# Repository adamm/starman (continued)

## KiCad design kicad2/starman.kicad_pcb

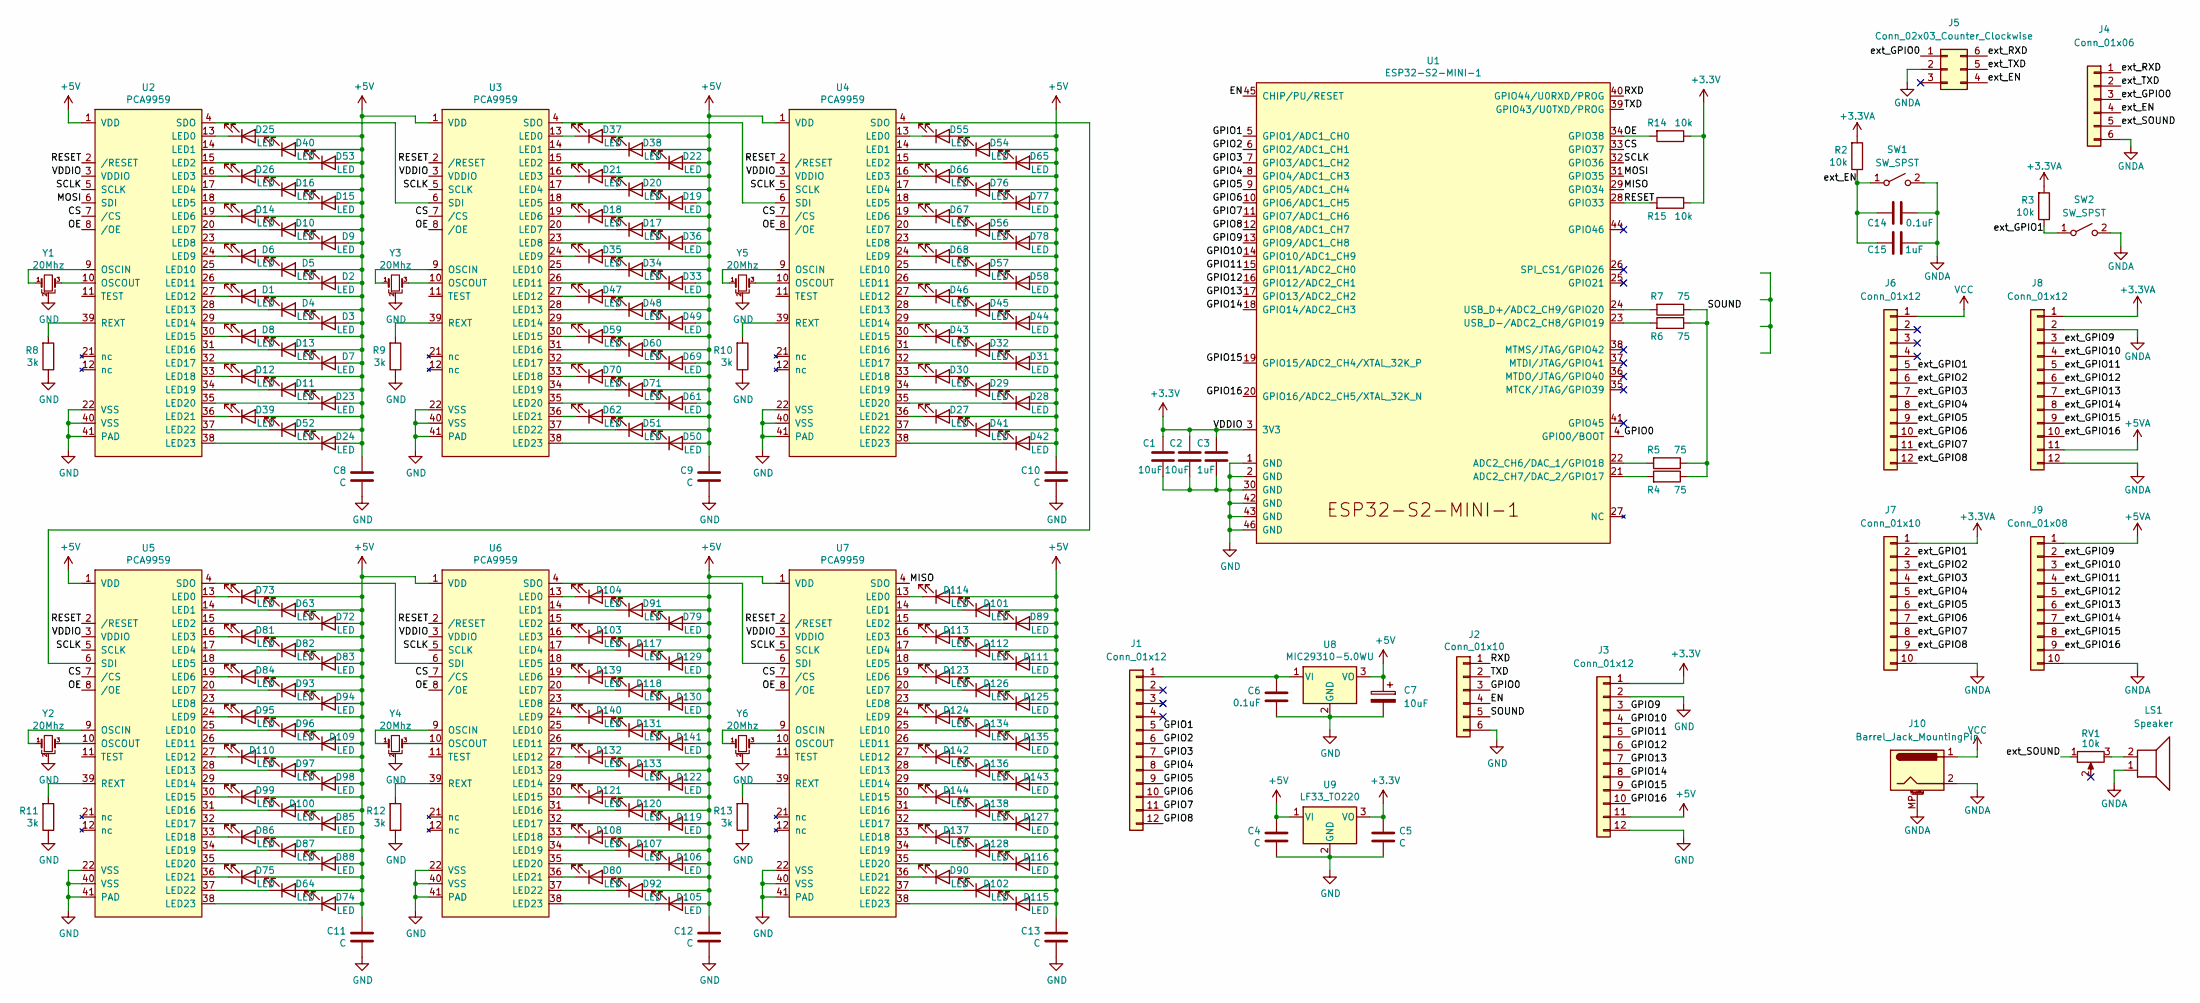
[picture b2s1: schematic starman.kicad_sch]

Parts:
C1, C2: 10uF; C_0805_2012Metric
C3, C15: 1uF; C_0805_2012Metric
C4, C5, C8, C9, C10, C11, C12, C13: C; C_0805_2012Metric
C6, C14: 0.1uF; C_0805_2012Metric
C7: 10uF; CP_EIA-3216-10_Kemet-I
D1, D2, D3, D4, D5, D6, D7, D8, D9, D10, D11, D12, D13, D14, D15, D16, D17, D18, D19, D20, D21, D22, D23, D24, D25, D26, D27, D28, D29, D30, D31, D32, D33, D34, D35, D36, D37, D38, D39, D40, D41, D42, D43, D44, D45, D46, D47, D48, D49, D50, D51, D52, D53, D54, D55, D56, D57, D58, D59, D60, D61, D62, D63, D64, D65, D66, D67, D68, D69, D70, D71, D72, D73, D74, D75, D76, D77, D78, D79, D80, D81, D82, D83, D84, D85, D86, D87, D88, D89, D90, D91, D92, D93, D94, D95, D96, D97, D98, D99, D100, D101, D102, D103, D104, D105, D106, D107, D108, D109, D110, D111, D112, D113, D114, D115, D116, D117, D118, D119, D120, D121, D122, D123, D124, D125, D126, D127, D128, D129, D130, D131, D132, D133, D134, D135, D136, D137, D138, D139, D140, D141, D142, D143, D144: LED; LED_Osram_Lx_P47F_D2mm_ReverseMount
J1: Conn_01x12; PinSocket_1x12_P2.54mm_Vertical_SMD_Pin1Right
J2: Conn_01x10; PinSocket_1x06_P2.54mm_Vertical_SMD_Pin1Left
J3: Conn_01x12; PinSocket_1x12_P2.54mm_Vertical_SMD_Pin1Left
J4: Conn_01x06; PinHeader_1x06_P2.54mm_Vertical
J5: Conn_02x03_Counter_Clockwise; PinHeader_2x03_P2.54mm_Vertical
J6, J8: Conn_01x12; PinHeader_1x12_P2.54mm_Vertical
J7: Conn_01x10; PinHeader_1x10_P2.54mm_Vertical
J9: Conn_01x08; PinHeader_1x10_P2.54mm_Vertical
J10: Barrel_Jack_MountingPin; BarrelJack_CUI_PJ-063AH_Horizontal
LS1: Speaker; MagneticBuzzer_StarMicronics_HMB-06_HMB-12
R2, R3, R14, R15: 10k; R_0805_2012Metric
R4, R5, R6, R7: 75; R_0805_2012Metric
R8, R9, R10, R11, R12, R13: 3k; R_0805_2012Metric
RV1: 10k; Potentiometer_ACP_CA9-VSMD_Vertical
SW1, SW2: SW_SPST; SW_SPST_PTS810
U1: ESP32-S2-MINI-1
U2, U3, U4, U5, U6, U7: PCA9959; QFN-40_EP_5x5_Pitch0.4mm
U8: MIC29310-5.0WU; TO-263-3_TabPin2
U9: LF33_TO220; SOT-223-3_TabPin2
Y1, Y2, Y3, Y4, Y5, Y6: 20Mhz; Resonator_SMD_muRata_CSTxExxV-3Pin_3.0x1.1mm

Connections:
+3.3VA: J7.1, J8.1, R2.2, R3.2
+3V3: C1.2, C2.2, C3.2, C5.2, J3.1, R14.1, R15.1, U1.3 (3V3), U2.3 (VDDIO), U3.3 (VDDIO), U4.3 (VDDIO), U5.3 (VDDIO), U6.3 (VDDIO), U7.3 (VDDIO), U9.3 (VO)
+5V: C4.2, C7.1, C8.2, C9.2, C10.2, C11.2, C12.2, C13.2, D1.2 (A), D2.2 (A), D3.2 (A), D4.2 (A), D5.2 (A), D6.2 (A), D7.2 (A), D8.2 (A), D9.2 (A), D10.2 (A), D11.2 (A), D12.2 (A), D13.2 (A), D14.2 (A), D15.2 (A), D16.2 (A), D17.2 (A), D18.2 (A), D19.2 (A), D20.2 (A), D21.2 (A), D22.2 (A), D23.2 (A), D24.2 (A), D25.2 (A), D26.2 (A), D27.2 (A), D28.2 (A), D29.2 (A), D30.2 (A), D31.2 (A), D32.2 (A), D33.2 (A), D34.2 (A), D35.2 (A), D36.2 (A), D37.2 (A), D38.2 (A), D39.2 (A), D40.2 (A), D41.2 (A), D42.2 (A), D43.2 (A), D44.2 (A), D45.2 (A), D46.2 (A), D47.2 (A), D48.2 (A), D49.2 (A), D50.2 (A), D51.2 (A), D52.2 (A), D53.2 (A), D54.2 (A), D55.2 (A), D56.2 (A), D57.2 (A), D58.2 (A), D59.2 (A), D60.2 (A), D61.2 (A), D62.2 (A), D63.2 (A), D64.2 (A), D65.2 (A), D66.2 (A), D67.2 (A), D68.2 (A), D69.2 (A), D70.2 (A), D71.2 (A), D72.2 (A), D73.2 (A), D74.2 (A), D75.2 (A), D76.2 (A), D77.2 (A), D78.2 (A), D79.2 (A), D80.2 (A), D81.2 (A), D82.2 (A), D83.2 (A), D84.2 (A), D85.2 (A), D86.2 (A), D87.2 (A), D88.2 (A), D89.2 (A), D90.2 (A), D91.2 (A), D92.2 (A), D93.2 (A), D94.2 (A), D95.2 (A), D96.2 (A), D97.2 (A), D98.2 (A), D99.2 (A), D100.2 (A), D101.2 (A), D102.2 (A), D103.2 (A), D104.2 (A), D105.2 (A), D106.2 (A), D107.2 (A), D108.2 (A), D109.2 (A), D110.2 (A), D111.2 (A), D112.2 (A), D113.2 (A), D114.2 (A), D115.2 (A), D116.2 (A), D117.2 (A), D118.2 (A), D119.2 (A), D120.2 (A), D121.2 (A), D122.2 (A), D123.2 (A), D124.2 (A), D125.2 (A), D126.2 (A), D127.2 (A), D128.2 (A), D129.2 (A), D130.2 (A), D131.2 (A), D132.2 (A), D133.2 (A), D134.2 (A), D135.2 (A), D136.2 (A), D137.2 (A), D138.2 (A), D139.2 (A), D140.2 (A), D141.2 (A), D142.2 (A), D143.2 (A), D144.2 (A), J3.11, U2.1 (VDD), U3.1 (VDD), U4.1 (VDD), U5.1 (VDD), U6.1 (VDD), U7.1 (VDD), U8.3 (VO), U9.1 (VI)
+5VA: J8.11, J9.1
/CS: U1.33 (GPIO37), U2.7 (/CS), U3.7 (/CS), U4.7 (/CS), U5.7 (/CS), U6.7 (/CS), U7.7 (/CS)
/EN: J2.4, U1.45 (CHIP/PU/RESET)
/GPIO0: J2.3, U1.4 (GPIO0/BOOT)
/GPIO1: J1.5, U1.5 (GPIO1/ADC1_CH0)
/GPIO2: J1.6, U1.6 (GPIO2/ADC1_CH1)
/GPIO3: J1.7, U1.7 (GPIO3/ADC1_CH2)
/GPIO4: J1.8, U1.8 (GPIO4/ADC1_CH3)
/GPIO5: J1.9, U1.9 (GPIO5/ADC1_CH4)
/GPIO6: J1.10, U1.10 (GPIO6/ADC1_CH5)
/GPIO7: J1.11, U1.11 (GPIO7/ADC1_CH6)
/GPIO8: J1.12, U1.12 (GPIO8/ADC1_CH7)
/GPIO9: J3.3, U1.13 (GPIO9/ADC1_CH8)
/GPIO10: J3.4, U1.14 (GPIO10/ADC1_CH9)
/GPIO11: J3.5, U1.15 (GPIO11/ADC2_CH0)
/GPIO12: J3.6, U1.16 (GPIO12/ADC2_CH1)
/GPIO13: J3.7, U1.17 (GPIO13/ADC2_CH2)
/GPIO14: J3.8, U1.18 (GPIO14/ADC2_CH3)
/GPIO15: J3.9, U1.19 (GPIO15/ADC2_CH4/XTAL_32K_P)
/GPIO16: J3.10, U1.20 (GPIO16/ADC2_CH5/XTAL_32K_N)
/MISO: U1.29 (GPIO34), U7.4 (SDO)
/MOSI: U1.31 (GPIO35), U2.6 (SDI)
/OE: R14.2, U1.34 (GPIO38), U2.8 (/OE), U3.8 (/OE), U4.8 (/OE), U5.8 (/OE), U6.8 (/OE), U7.8 (/OE)
/RESET: R15.2, U1.28 (GPIO33), U2.2 (/RESET), U3.2 (/RESET), U4.2 (/RESET), U5.2 (/RESET), U6.2 (/RESET), U7.2 (/RESET)
/RXD: J2.1, U1.40 (GPIO44/U0RXD/PROG)
/SCLK: U1.32 (GPIO36), U2.5 (SCLK), U3.5 (SCLK), U4.5 (SCLK), U5.5 (SCLK), U6.5 (SCLK), U7.5 (SCLK)
/SOUND: J2.5, R4.1, R5.1, R6.1, R7.1
/TXD: J2.2, U1.39 (GPIO43/U0TXD/PROG)
/ext_EN: C14.2, C15.2, J4.4, J5.4, R2.1, SW1.1 (A)
/ext_GPIO0: J4.3, J5.1
/ext_GPIO1: J6.5, J7.2, R3.1, SW2.1 (A)
/ext_GPIO2: J6.6, J7.3
/ext_GPIO3: J6.7, J7.4
/ext_GPIO4: J6.8, J7.5
/ext_GPIO5: J6.9, J7.6
/ext_GPIO6: J6.10, J7.7
/ext_GPIO7: J6.11, J7.8
/ext_GPIO8: J6.12, J7.9
/ext_GPIO9: J8.3, J9.2
/ext_GPIO10: J8.4, J9.3
/ext_GPIO11: J8.5, J9.4
/ext_GPIO12: J8.6, J9.5
/ext_GPIO13: J8.7, J9.6
/ext_GPIO14: J8.8, J9.7
/ext_GPIO15: J8.9, J9.8
/ext_GPIO16: J8.10, J9.9
/ext_RXD: J4.1, J5.6
/ext_SOUND: J4.5, RV1.1
/ext_TXD: J4.2, J5.5
GND: C1.1, C2.1, C3.1, C4.1, C5.1, C6.1, C7.2, C8.1, C9.1, C10.1, C11.1, C12.1, C13.1, J2.6, J3.2, J3.12, R8.1, R9.1, R10.1, R11.1, R12.1, R13.1, U1.1 (GND), U1.2 (GND), U1.30 (GND), U1.42 (GND), U1.43 (GND), U1.46 (GND), U2.22 (VSS), U2.40 (VSS), U2.41 (PAD), U3.22 (VSS), U3.40 (VSS), U3.41 (PAD), U4.22 (VSS), U4.40 (VSS), U4.41 (PAD), U5.22 (VSS), U5.40 (VSS), U5.41 (PAD), U6.22 (VSS), U6.40 (VSS), U6.41 (PAD), U7.22 (VSS), U7.40 (VSS), U7.41 (PAD), U8.2 (GND), U9.2 (GND), Y1.2, Y2.2, Y3.2, Y4.2, Y5.2, Y6.2
GNDA: C14.1, C15.1, J4.6, J5.2, J7.10, J8.2, J8.12, J9.10, J10.2, J10.MP (MountPin), LS1.1, SW1.2 (B), SW2.2 (B)
unnamed: C6.2, J1.1, U8.1 (VI)
unnamed: D1.1 (K), U2.27 (LED12)
unnamed: D2.1 (K), U2.26 (LED11)
unnamed: D3.1 (K), U2.29 (LED14)
unnamed: D4.1 (K), U2.28 (LED13)
unnamed: D5.1 (K), U2.25 (LED10)
unnamed: D6.1 (K), U2.24 (LED9)
unnamed: D7.1 (K), U2.32 (LED17)
unnamed: D8.1 (K), U2.30 (LED15)
unnamed: D9.1 (K), U2.23 (LED8)
unnamed: D10.1 (K), U2.20 (LED7)
unnamed: D11.1 (K), U2.34 (LED19)
unnamed: D12.1 (K), U2.33 (LED18)
unnamed: D13.1 (K), U2.31 (LED16)
unnamed: D14.1 (K), U2.19 (LED6)
unnamed: D15.1 (K), U2.18 (LED5)
unnamed: D16.1 (K), U2.17 (LED4)
unnamed: D17.1 (K), U3.20 (LED7)
unnamed: D18.1 (K), U3.19 (LED6)
unnamed: D19.1 (K), U3.18 (LED5)
unnamed: D20.1 (K), U3.17 (LED4)
unnamed: D21.1 (K), U3.16 (LED3)
unnamed: D22.1 (K), U3.15 (LED2)
unnamed: D23.1 (K), U2.35 (LED20)
unnamed: D24.1 (K), U2.38 (LED23)
unnamed: D25.1 (K), U2.13 (LED0)
unnamed: D26.1 (K), U2.16 (LED3)
unnamed: D27.1 (K), U4.36 (LED21)
unnamed: D28.1 (K), U4.35 (LED20)
unnamed: D29.1 (K), U4.34 (LED19)
unnamed: D30.1 (K), U4.33 (LED18)
unnamed: D31.1 (K), U4.32 (LED17)
unnamed: D32.1 (K), U4.31 (LED16)
unnamed: D33.1 (K), U3.26 (LED11)
unnamed: D34.1 (K), U3.25 (LED10)
unnamed: D35.1 (K), U3.24 (LED9)
unnamed: D36.1 (K), U3.23 (LED8)
unnamed: D37.1 (K), U3.13 (LED0)
unnamed: D38.1 (K), U3.14 (LED1)
unnamed: D39.1 (K), U2.36 (LED21)
unnamed: D40.1 (K), U2.14 (LED1)
unnamed: D41.1 (K), U4.37 (LED22)
unnamed: D42.1 (K), U4.38 (LED23)
unnamed: D43.1 (K), U4.30 (LED15)
unnamed: D44.1 (K), U4.29 (LED14)
unnamed: D45.1 (K), U4.28 (LED13)
unnamed: D46.1 (K), U4.27 (LED12)
unnamed: D47.1 (K), U3.27 (LED12)
unnamed: D48.1 (K), U3.28 (LED13)
unnamed: D49.1 (K), U3.29 (LED14)
unnamed: D50.1 (K), U3.38 (LED23)
unnamed: D51.1 (K), U3.37 (LED22)
unnamed: D52.1 (K), U2.37 (LED22)
unnamed: D53.1 (K), U2.15 (LED2)
unnamed: D54.1 (K), U4.14 (LED1)
unnamed: D55.1 (K), U4.13 (LED0)
unnamed: D56.1 (K), U4.20 (LED7)
unnamed: D57.1 (K), U4.25 (LED10)
unnamed: D58.1 (K), U4.26 (LED11)
unnamed: D59.1 (K), U3.30 (LED15)
unnamed: D60.1 (K), U3.31 (LED16)
unnamed: D61.1 (K), U3.35 (LED20)
unnamed: D62.1 (K), U3.36 (LED21)
unnamed: D63.1 (K), U5.14 (LED1)
unnamed: D64.1 (K), U5.37 (LED22)
unnamed: D65.1 (K), U4.15 (LED2)
unnamed: D66.1 (K), U4.16 (LED3)
unnamed: D67.1 (K), U4.19 (LED6)
unnamed: D68.1 (K), U4.24 (LED9)
unnamed: D69.1 (K), U3.32 (LED17)
unnamed: D70.1 (K), U3.33 (LED18)
unnamed: D71.1 (K), U3.34 (LED19)
unnamed: D72.1 (K), U5.15 (LED2)
unnamed: D73.1 (K), U5.13 (LED0)
unnamed: D74.1 (K), U5.38 (LED23)
unnamed: D75.1 (K), U5.36 (LED21)
unnamed: D76.1 (K), U4.17 (LED4)
unnamed: D77.1 (K), U4.18 (LED5)
unnamed: D78.1 (K), U4.23 (LED8)
unnamed: D79.1 (K), U6.15 (LED2)
unnamed: D80.1 (K), U6.36 (LED21)
unnamed: D81.1 (K), U5.16 (LED3)
unnamed: D82.1 (K), U5.17 (LED4)
unnamed: D83.1 (K), U5.18 (LED5)
unnamed: D84.1 (K), U5.19 (LED6)
unnamed: D85.1 (K), U5.32 (LED17)
unnamed: D86.1 (K), U5.33 (LED18)
unnamed: D87.1 (K), U5.34 (LED19)
unnamed: D88.1 (K), U5.35 (LED20)
unnamed: D89.1 (K), U7.15 (LED2)
unnamed: D90.1 (K), U7.36 (LED21)
unnamed: D91.1 (K), U6.14 (LED1)
unnamed: D92.1 (K), U6.37 (LED22)
unnamed: D93.1 (K), U5.20 (LED7)
unnamed: D94.1 (K), U5.23 (LED8)
unnamed: D95.1 (K), U5.24 (LED9)
unnamed: D96.1 (K), U5.25 (LED10)
unnamed: D97.1 (K), U5.28 (LED13)
unnamed: D98.1 (K), U5.29 (LED14)
unnamed: D99.1 (K), U5.30 (LED15)
unnamed: D100.1 (K), U5.31 (LED16)
unnamed: D101.1 (K), U7.14 (LED1)
unnamed: D102.1 (K), U7.37 (LED22)
unnamed: D103.1 (K), U6.16 (LED3)
unnamed: D104.1 (K), U6.13 (LED0)
unnamed: D105.1 (K), U6.38 (LED23)
unnamed: D106.1 (K), U6.35 (LED20)
unnamed: D107.1 (K), U6.34 (LED19)
unnamed: D108.1 (K), U6.33 (LED18)
unnamed: D109.1 (K), U5.26 (LED11)
unnamed: D110.1 (K), U5.27 (LED12)
unnamed: D111.1 (K), U7.18 (LED5)
unnamed: D112.1 (K), U7.17 (LED4)
unnamed: D113.1 (K), U7.16 (LED3)
unnamed: D114.1 (K), U7.13 (LED0)
unnamed: D115.1 (K), U7.38 (LED23)
unnamed: D116.1 (K), U7.35 (LED20)
unnamed: D117.1 (K), U6.17 (LED4)
unnamed: D118.1 (K), U6.20 (LED7)
unnamed: D119.1 (K), U6.32 (LED17)
unnamed: D120.1 (K), U6.31 (LED16)
unnamed: D121.1 (K), U6.30 (LED15)
unnamed: D122.1 (K), U6.29 (LED14)
unnamed: D123.1 (K), U7.19 (LED6)
unnamed: D124.1 (K), U7.24 (LED9)
unnamed: D125.1 (K), U7.23 (LED8)
unnamed: D126.1 (K), U7.20 (LED7)
unnamed: D127.1 (K), U7.32 (LED17)
unnamed: D128.1 (K), U7.34 (LED19)
unnamed: D129.1 (K), U6.18 (LED5)
unnamed: D130.1 (K), U6.23 (LED8)
unnamed: D131.1 (K), U6.25 (LED10)
unnamed: D132.1 (K), U6.27 (LED12)
unnamed: D133.1 (K), U6.28 (LED13)
unnamed: D134.1 (K), U7.25 (LED10)
unnamed: D135.1 (K), U7.26 (LED11)
unnamed: D136.1 (K), U7.28 (LED13)
unnamed: D137.1 (K), U7.33 (LED18)
unnamed: D138.1 (K), U7.31 (LED16)
unnamed: D139.1 (K), U6.19 (LED6)
unnamed: D140.1 (K), U6.24 (LED9)
unnamed: D141.1 (K), U6.26 (LED11)
unnamed: D142.1 (K), U7.27 (LED12)
unnamed: D143.1 (K), U7.29 (LED14)
unnamed: D144.1 (K), U7.30 (LED15)
unnamed: R4.2, U1.21 (ADC2_CH7/DAC_2/GPIO17)
unnamed: R5.2, U1.22 (ADC2_CH6/DAC_1/GPIO18)
unnamed: R6.2, U1.23 (USB_D-/ADC2_CH8/GPIO19)
unnamed: R7.2, U1.24 (USB_D+/ADC2_CH9/GPIO20)
unnamed: R8.2, U2.39 (REXT)
unnamed: R9.2, U3.39 (REXT)
unnamed: R10.2, U4.39 (REXT)
unnamed: R11.2, U5.39 (REXT)
unnamed: R12.2, U6.39 (REXT)
unnamed: R13.2, U7.39 (REXT)
unnamed: LS1.2, RV1.3
unnamed: U2.4 (SDO), U3.6 (SDI)
unnamed: U2.9 (OSCIN), Y1.1
unnamed: U2.10 (OSCOUT), Y1.3
unnamed: U3.4 (SDO), U4.6 (SDI)
unnamed: U3.9 (OSCIN), Y3.1
unnamed: U3.10 (OSCOUT), Y3.3
unnamed: U4.4 (SDO), U5.6 (SDI)
unnamed: U4.9 (OSCIN), Y5.1
unnamed: U4.10 (OSCOUT), Y5.3
unnamed: U5.4 (SDO), U6.6 (SDI)
unnamed: U5.9 (OSCIN), Y2.1
unnamed: U5.10 (OSCOUT), Y2.3
unnamed: U6.4 (SDO), U7.6 (SDI)
unnamed: U6.9 (OSCIN), Y4.1
unnamed: U6.10 (OSCOUT), Y4.3
unnamed: U7.9 (OSCIN), Y6.1
unnamed: U7.10 (OSCOUT), Y6.3
VCC: J6.1, J10.1

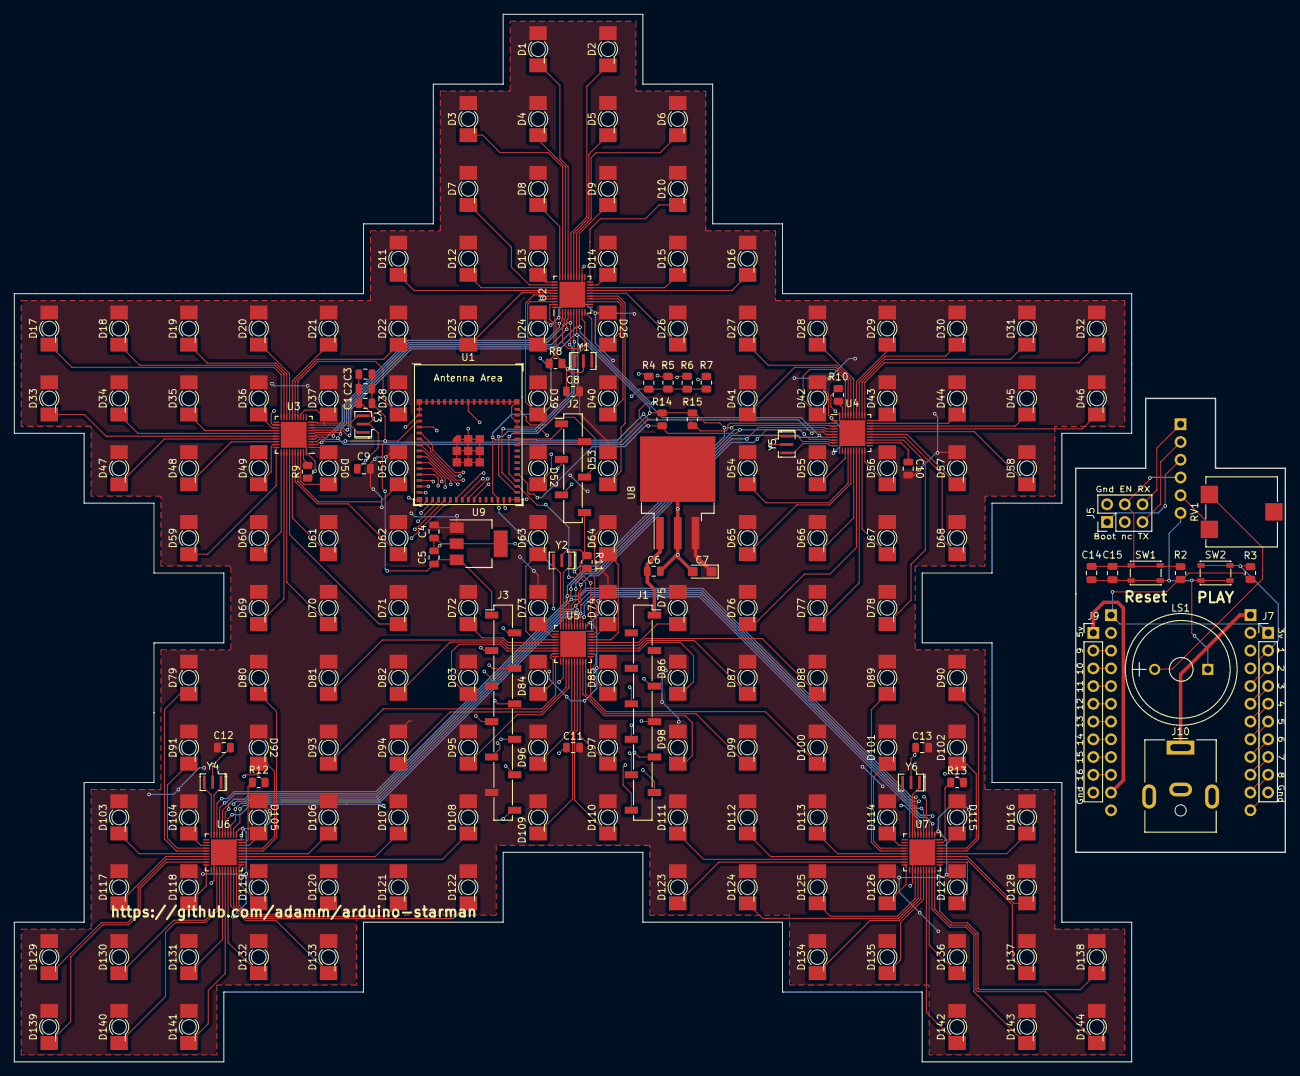
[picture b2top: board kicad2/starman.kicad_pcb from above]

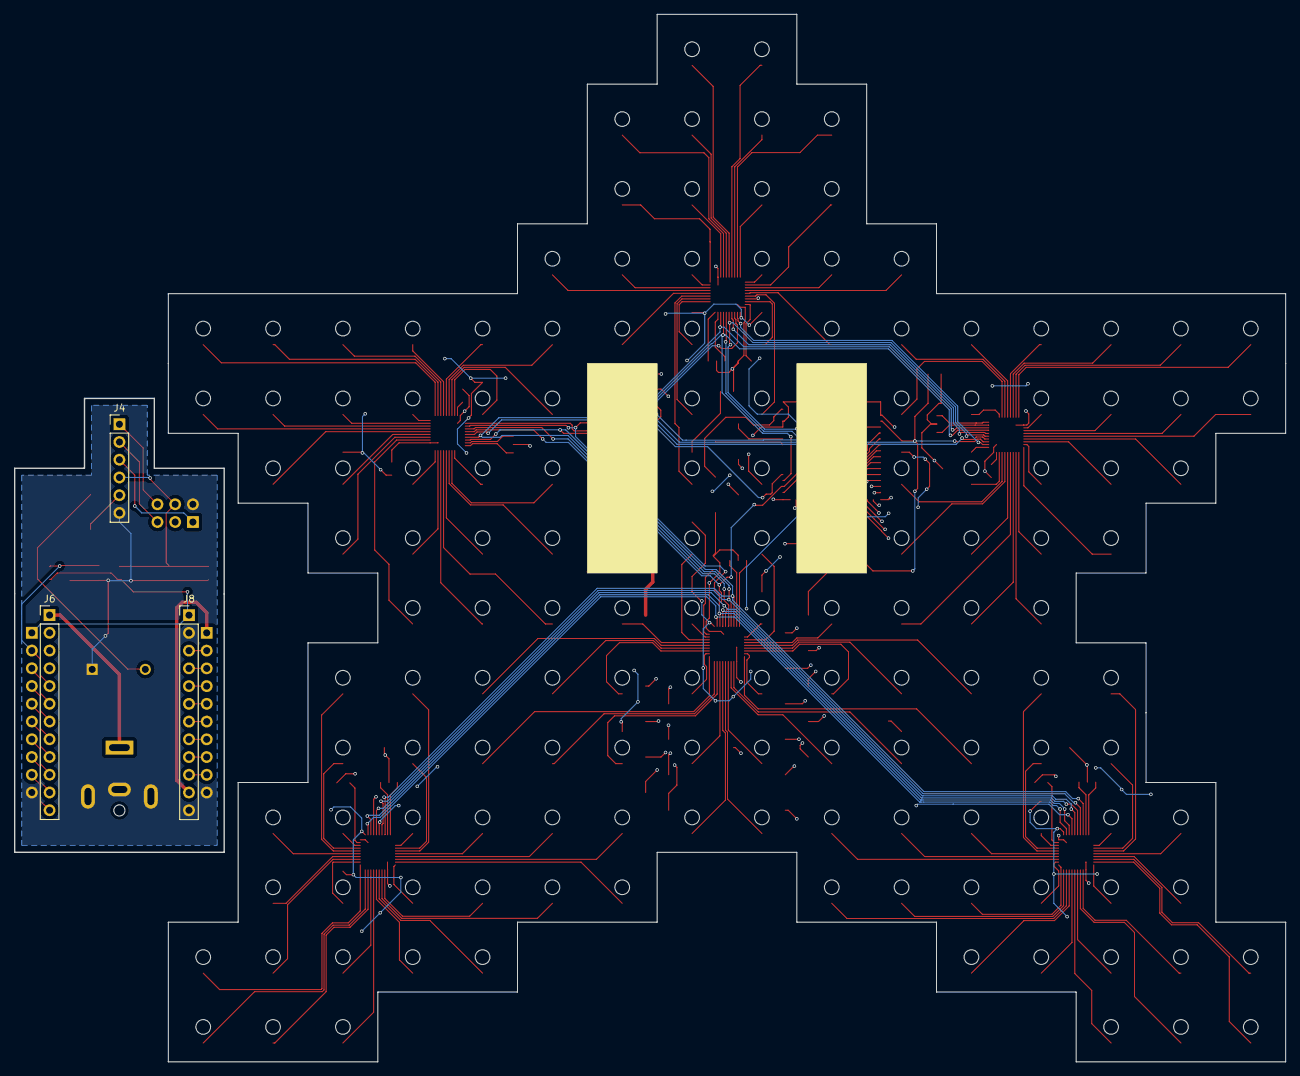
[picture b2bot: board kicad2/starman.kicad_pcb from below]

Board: 4 copper layers, 160.0 x 150.0 mm, 202 parts (3 on the bottom side), 228 nets.

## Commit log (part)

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2018-12-09 Updated the INO header
2018-12-09 Initial version of sparkly then crazy starman light array
2018-12-09 Include GNUv3 license to main code
    Adafruit TLC5947 code uses BSD license
2018-12-09 More README
2018-12-09 Include Playtune library
2018-12-15 Added Mario music tracks
    Converted from mariopiano.com MIDIs into C using converter at
    https://github.com/lenshustek/miditones
2018-12-15 Removed unused code, minor formatting adjustments
2018-12-16 Force a hardware reset after playback.
    For some reason, attachInterrupt() conflicts with pt.initchan()
    functions to the point after 2 or 3 music loops, the arduino hard-locks.
    As a workaround, execute a hardware reset after each loop. Not ideal
    but good enough: we don't need to track the state between runs.
2018-12-16 Add in additional music, and different sequencing/patterns based on the music being played
2021-11-28 Convert the playtune library to ESP32
    Based upon Teensy version created by original author
2021-11-28 Fixed crash under some marquee patterns (buffer overflow); also removed button interrupt (was overkill, caused crashes)
2021-11-29 Updated Overworld to SMBW version
2021-12-01 Strange bug where underwater crashes esp32 when debug logs are printed
    Need to figure out what\'s going on, but until then, just disable the logs!
2021-12-01 Add on a very basic webserver
2021-12-02 Add on ArduinoOTA support
    Becuase I don't want to climb up the tree with a usb cable to update the program
2021-12-08 Rewrite playback logic to better follow playing a game, and random events occur within.
2021-12-08 Added 1up music and pattern
2021-12-12 PCB to handle the ESP32 and speaker components.
2021-12-12 Minor adjustments to resistors and some placements
2021-12-14 Transition to standard ESP32 DevKit mounting
2021-12-14 Begin SM64 playlist
2021-12-18 Final placement modifications, off to PCB house!
2021-12-26 Minor resistor updates to align with real build
2022-04-10 Placements of components and things
2022-04-10 Route U2 and U3 LEDs
2022-04-14 Added mounting headers -- will move barrel jack and usb to daughter board
2022-05-02 Added daughter board for power and buttons
2022-05-24 Fixed DRC errors
2022-08-01 Removed simple hardware POC
2022-08-01 Added some neat logos, fixed potentiometer
2022-08-02 Identify candidates for mounting components
2022-08-05 Added KiCad and OSHW logos
2022-08-11 Fixed DRC, restored logos, fixed github url
2022-08-22 Updated part numbers for Y1..Y6, U8
2022-08-27 Set mask clearance to 0.22mm
2022-08-29 Run DRC, correct for spacing -- Fixed +5V to C11, D97, D110
    WARNING: there is a risk that C11 and D97 and D110 are not connected to
    +5V as this design already went for production. A bodge wire may be needed.
    At least its fixed for any future builds
2022-09-12 Fixed the orientation of J5, moved GND plane to top copper
2022-09-15 Move from NCP59301 to AP1084
    Cheaper and provides 5V 5A
2022-09-17 Change U11 AP1084 to AZ1084CS2-ADJ (due to stock)
2022-09-17 Re-run ERC, DRC
2022-09-18 Fillet the SPI lines
2022-09-19 Added placeholders for low-pass filters for SCLK, LE pins -- just incase of poor signal quality
    Populate with 100Ω and 150pF, respectively
2022-09-19 Updated some silkscreen on ext module
2022-09-21 Add on a power switch and status light
2022-09-22 Upgrade from IS31AP4991-SLS2 to PAM8302AAS
2022-09-24 Added band-pass filter into PCB
2022-09-27 Added on an optional mosfet and power switch
2022-09-29 Updated espressif kicad libraries
2022-09-29 Move legacy code that needs to be ported into an legacy folder
2022-09-29 Added amp IC and speaker data sheets
2022-09-30 Updated README for v2
2022-09-30 Remove legacy C++ Playtune code now that esp32 version is working
2022-10-02 Adding in status LED support (WS2812) for future OTA and DLC updates
2022-10-04 Add on some preliminary light patterns
2022-10-05 Updated README, .gitignore, 3rd party component path
2022-10-06 Adjust component placement around U13
2022-10-06 Vacate ground plane of signal traces
2022-10-08 Created a 3d-printed mount to better secure the star to the top of the tree
2022-10-08 Convert BOM from HTML to CSV
    The ibom plugin is cool but it's pretty bloated
2022-10-09 Adding in Play button support using GPIO interrupt
2022-10-09 Remove legacy arduino codebase as all core logic now implemented in this version. (UAT pending!)
2022-10-11 Create LED look-up table (LUT) to match the pattern pixel with the physical LED location in the level shift array
2022-10-16 Send LED pattern data to the LED1642GW buffer
2022-10-16 Send the pattern framebuffer to the LEDs on each musical note
2022-10-17 Sparkle Sparkle!
    Implement separate thread to show a sparkle animation while we wait for
    someone to press the play button.
2022-10-18 Use a constant incremnting sparkle step rate
2022-10-19 Ensure all sound channels are set to output and at zero level
2022-10-19 Cleanup .vscode
2022-10-22 Let there be light!
2022-10-22 Slow down the idle-sparkle routine a bit
2022-10-23 Fix the look-up table between the level-shift array position to the physical LED position
2022-10-24 Redo scroll() and rotate() pattern functions
2022-10-24 Put a cap on the LED gain at 50.
    Exceeding that could overheat the board when all lights are on full power
2022-10-24 Use Conway's Game of Life as engine for animating specific patterns
2022-10-26 Debug the waves and sweep pattern orientations
2022-10-26 Split the flagpole and course_clear music, allowing for a pattern change
2022-10-27 Standardize on pattern and display struct typedefs
    This will allow for better support for larger scrolling patterns
2022-10-28 Fixed an issue where the sparkle spontaneously stops for ~600 ticks
2022-10-29 Disable the WS2812B status light as there isn't an RMT channel available to utilize it :(
    Maybe the protocol be simulated via SPI? Will figure that out later.
    For now just drop support for the WS2812B LED at D145
2022-10-30 Starting framework for showing text on the display
2022-10-31 Reroute and fillet GPIO 38 into a straighter net
    Hopefully this will resolve communication issues to the WS2812B at D145
2022-11-02 Update the font to align with ascii characters at positions 32-96
    This will make calculating the position within the font data struct
    easier. Also if we want to expand to lower-case letters it'l be
    trivial to exptend font to characters 97-122
2022-11-03 WIP: RGB LED debug
2022-11-03 Move the "Game Over" text into a gameover pattern
2022-11-06 Scroll the "GAME OVER" text independently of the music
2022-11-07 Adjusted mount riser placements and cone width
2022-11-09 Isolate the display framebuffer into background, overlay, and text layers
2022-11-12 Updated README and created BUILDING instructions
2022-11-12 Create github action to automate build
2022-11-12 Revert "Use local instance of firmware server for testing"
    This reverts commit 7f949fbbcf99c1bf262ee8d2536232a2103268e7.
2022-11-12 As OTA update being downloaded, report the progress as a percentage
2022-11-12 Scroll the IP address on the display during the sparkle routine
2022-11-13 Simplify device AP name when provisioning
2022-11-13 Outsource wifi management to the "esp32-wifi-manager" component
    Super convenient OSS/MIT-licensed library. Original source at:
    https://github.com/tonyp7/esp32-wifi-manager
2022-11-13 Add an "HTTP GET /play" endpoint to play the game.
    Starting framework to interact with the star via the web site
2022-11-13 Add on a phototransistor to detect ambient light
    Allows for dynamic brightness control by reading the light and adjusting
    the LED1642W gain on the fly.
    TODO: Analogue read on GPIO2 pending
2022-11-15 Use a photoresistor on GPIO4 to perform ambient light detection via ADC
    This will be used to set the display LED brightness, so the display is
    not blinding at nighttime.
2022-11-16 Deprecate ESP32C3 config -- only support ESP32S3 and ESP32S3
    Not enought GPIO pins on ESP32C3, and it never worked as well with all
    the PWM music channels
2022-11-16 Send a shutdown signal to the sparkle task when the system transistions from sparkle mode to play mode.
    This is needed because of a race condition that can be encountered if
    the user presses PLAY while the system is in the middle of calling
    sparkle_task->display_update_leds() and sending data to the led1642gw
    drivers.
    If we abruptly kill the sparkle_task, the led1642gw_lock could remain
    active and will never clear, causing the system to deadlock as soon as
2022-11-16 Provide a /status.json endpoint for reporting the game status to the user via HTTP API
2022-11-16 GROSS! VScode hides tabs!?
    Convert all tabs to 4 spaces as project standard.
2022-11-17 Updated upstream espressif footprints
2022-11-18 Disable the web app Play button while the game is playing
2022-11-18 Start the game at level 1, not 0; increment level only once successful
2022-11-20 Minor formatting fixes for internal web page
2022-11-20 Revert "Remove RGB light code from 2.1 release"
    This reverts commit c239d038574806586f622f953d560291dd0ff6ce and
    restores RGB code into this branch.
2022-11-20 Serve the about.html webpage
2022-11-20 Get/set brightness from web app to led1642gw and save value to NVS storage
    If brightness is set to -1, use the photocell to set brightness relative
    to ambient light.
2022-11-21 Raise maximum gain to 100
    The peak draw with all pixels on @ 100 gain, plus sound and animation,
    is 1.4A, well below the 2A power brick purchased.
    LED1642GW chip temp reaches 50˚C though, so after some stress tests it
    may still be lowered to 80 or 75.
2022-11-22 Push text to display via POST /text
2022-11-24 If the player is destined to finish the level, cut the music off at a random point in the last half of the song
2022-11-25 Make SMB3/SMW themes available
2022-11-27 Create a GET /reset endpoint to trigger a device reset via HTTP REST
2022-11-27 Cleaned up http GET and POST passthrough logic
    Fixes false-positive 404 errors being sent
2022-11-30 Updated README with project status, known issues
2022-11-30 Use new OTA URL structure of https://starman.array.org/firmware/${track}.bin
2022-12-01 If warning music is shown, play it in the last 1/3rd of the stage music
2022-12-01 Fix an issue where note duration is mis-interpreted as the end of the song (0xF0)
2022-12-03 Updated documentation for Installation, Wifi Setup, and Known Issues
2022-12-06 Allow for theme-specific game logic
2022-12-10 Include esp-idf's compile-commands.json into .vscode's c_cpp_properties.json's compileCommands key
    VSCode did this automatically, unsure why or what it acutally provides :)
2022-12-14 Better separation of LOZ theme logic
2022-12-19 Implement the Genie
2022-12-23 Replace malloc() with calloc()
2022-12-24 Clean up SMW's bonus, course clear tracks
2022-12-24 Clean up smw_course_clear, add smw_coin
2022-12-24 Leverage the "1up" sound in LOZ as "find a secret door"
2023-01-07 Begin work on the Tetᴙis theme.
2023-01-08 Activate the tetris theme music and background patterns
2023-01-09 Added missing "S" and "Z" blocks
    I cannot believe I forgot them
2023-12-02 Updated schematcs/pcb for KiCad 7.0
2023-12-03 Use a working jquery CDN
2023-12-03 Play some sounds as the OTA firmware update is downloaded/installed
2023-12-04 Add logic to rotate through the themes though button short/long presses
    - Long-press to go into theme-select mode
    - Short-press to change themes
    - Long-press to save the theme and return to game mode
2023-12-08 Add a timer to identify a long-press while the button is depressed
2023-12-08 Cleanup theme format and prep for SMBW
2023-12-09 Call /test/$(theme)/$(stage_num) to allow for playback of specific music/themes on the fly.
2023-12-09 Finalize SMBW music for DLC
2023-12-12 Adjust the mount to fit more snugly between the starman PCBs
2023-12-17 Replace wonder level 3 with maw-maw-mouthful
2023-12-19 Commit SM64 theme music
2023-12-24 Slower down the flicker during invert_background() routine.
2023-12-29 Adjusted font bitmap to be a little clearer
2024-04-30 Normalized schematics for printing
2024-05-02 Clean up SMB2 clear, fanfare, death tracks; add smb3 warpzone instead of starman
    Also disabled warning tone on SMB2
